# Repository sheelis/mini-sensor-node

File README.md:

# wifi water level transmitter

## Parts:

ESP-WROOM-02 connected to wifi and serving a page, also can send readings to some other server
HC-S04 for distance
DS18B20 for temperature?

## info

how to program ESP-WROOM-02
https://learn.edwinrobotics.com/getting-started-with-esp-wroom-02/
https://www.espressif.com/sites/default/files/documentation/0c-esp-wroom-02_datasheet_en.pdf

3.3v with HC-SR04
https://www.letscontrolit.com/wiki/index.php/HC-SR04

US reading on esp
https://github.com/asksensors/AskSensors-ESP8266-Ultrasonic/blob/master/ultrasonic_http.ino
http://www.esp8266learning.com/wemos-mini-hc-sr04-ultrasonic-sensor.php

https://www.youtube.com/watch?v=Q0eUoFIXrWE

## plan

- kicad and cnc a pcb
- solder on parts
- attach 3.3v transformer
- program blink on esp
- attach US, read distance
- design interface: wifi ap or send to remote server?
- code the transmission, storage, logging

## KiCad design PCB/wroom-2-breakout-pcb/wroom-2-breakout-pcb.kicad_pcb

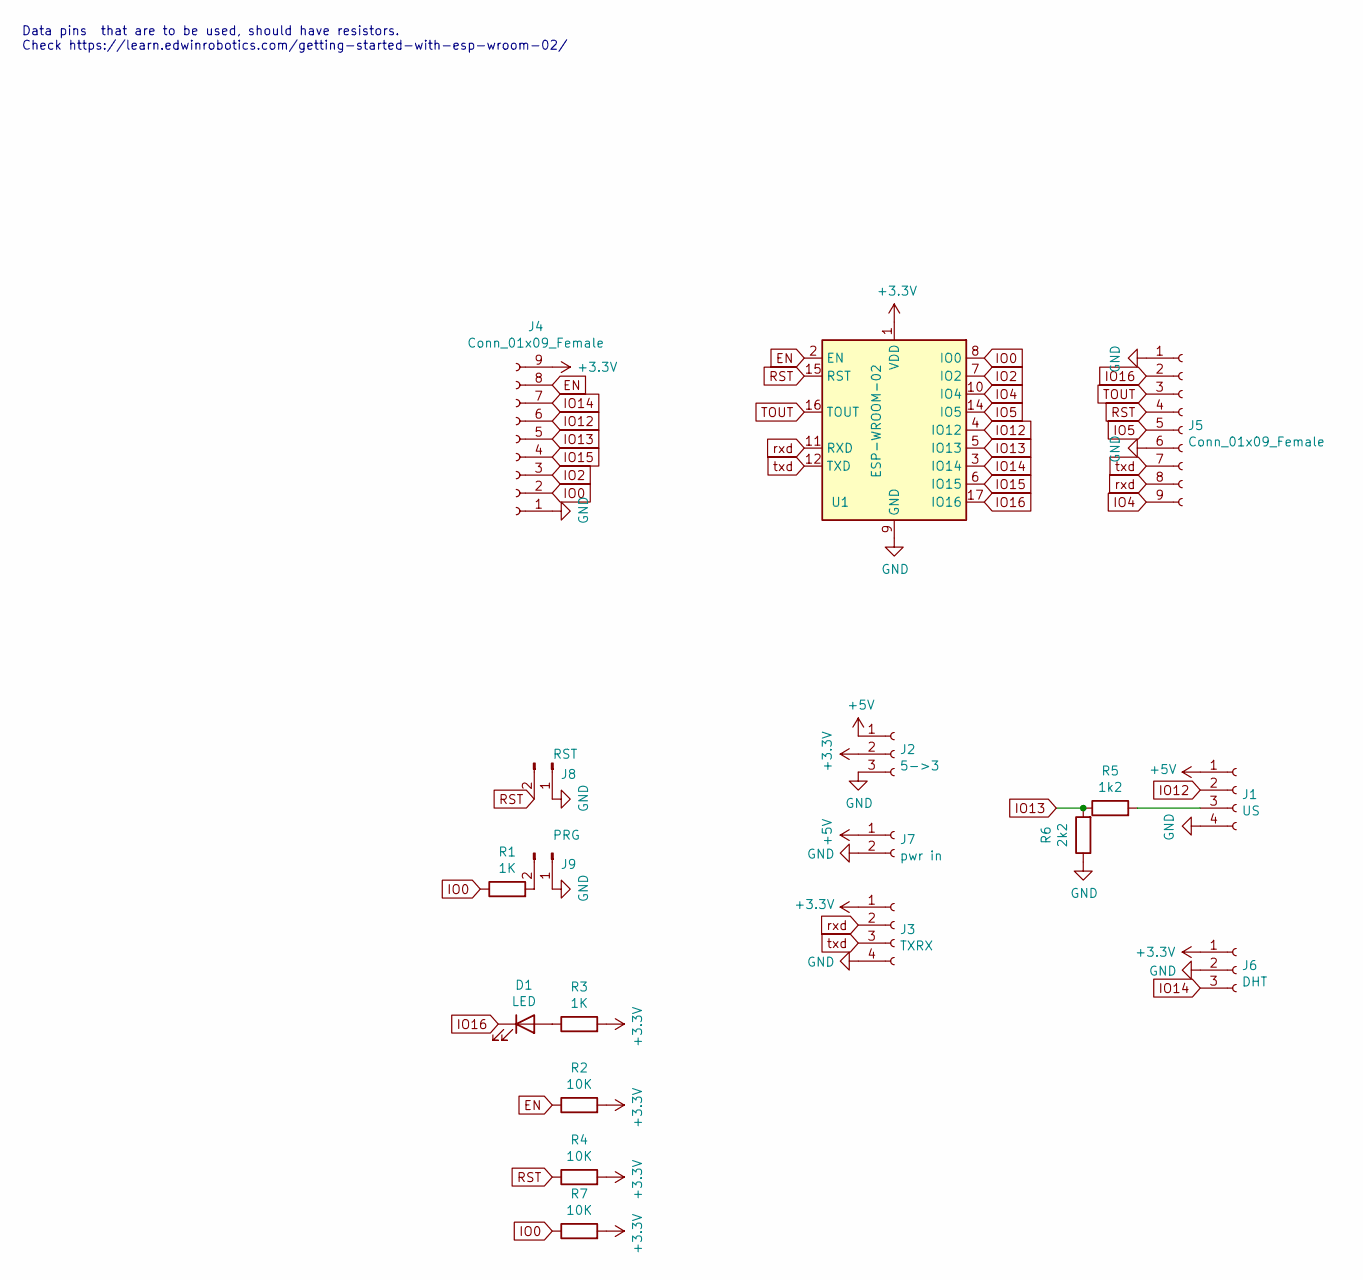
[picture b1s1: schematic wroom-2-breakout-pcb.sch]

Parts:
D1: LED; LED_D3.0mm
J1: US; PinSocket_1x04_P2.54mm_Vertical
J2: 5->3; PinSocket_1x03_P2.54mm_Vertical
J3: TXRX; PinHeader_1x04_P2.54mm_Vertical
J4, J5: Conn_01x09_Female; PinHeader_1x09_P2.54mm_Vertical
J6: DHT; PinHeader_1x03_P2.54mm_Vertical
J7: pwr in; PinHeader_1x02_P2.54mm_Vertical
J8: RST; PinHeader_1x02_P2.54mm_Vertical
J9: PRG; PinHeader_1x02_P2.54mm_Vertical
R1, R3: 1K; R_Axial_DIN0207_L6.3mm_D2.5mm_P7.62mm_Horizontal
R2, R4, R7: 10K; R_Axial_DIN0207_L6.3mm_D2.5mm_P7.62mm_Horizontal
R5: 1k2; R_Axial_DIN0207_L6.3mm_D2.5mm_P7.62mm_Horizontal
R6: 2k2; R_Axial_DIN0207_L6.3mm_D2.5mm_P7.62mm_Horizontal
U1: ESP-WROOM-02

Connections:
+3V3: J2.2, J3.1, J4.9, J6.1, R2.2, R3.2, R4.2, R7.2, U1.1 (VDD)
+5V: J1.1, J2.1, J7.1
EN: J4.8, R2.1, U1.2 (EN)
GND: J1.4, J2.3, J3.4, J4.1, J5.1, J5.6, J6.2, J7.2, J8.1, J9.1, R6.1, U1.9 (GND), U1.13 (GND), U1.18 (GND), U1.19 (GND)
IO0: J4.2, R1.1, R7.1, U1.8 (IO0)
IO2: J4.3, U1.7 (IO2)
IO4: J5.9, U1.10 (IO4)
IO5: J5.5, U1.14 (IO5)
IO12: J1.2, J4.6, U1.4 (IO12)
IO13: J4.5, R5.1, R6.2, U1.5 (IO13)
IO14: J4.7, J6.3, U1.3 (IO14)
IO15: J4.4, U1.6 (IO15)
IO16: D1.1 (K), J5.2, U1.17 (IO16)
unnamed: D1.2 (A), R3.1
unnamed: J1.3, R5.2
unnamed: J9.2, R1.2
RST: J5.4, J8.2, R4.1, U1.15 (RST)
TOUT: J5.3, U1.16 (TOUT)
rxd: J3.2, J5.8, U1.11 (RXD)
txd: J3.3, J5.7, U1.12 (TXD)

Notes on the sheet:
Data pins that are to be used, should have resistors. Check https://learn.edwinrobotics.com/getting-started-with-esp-wroom-02/

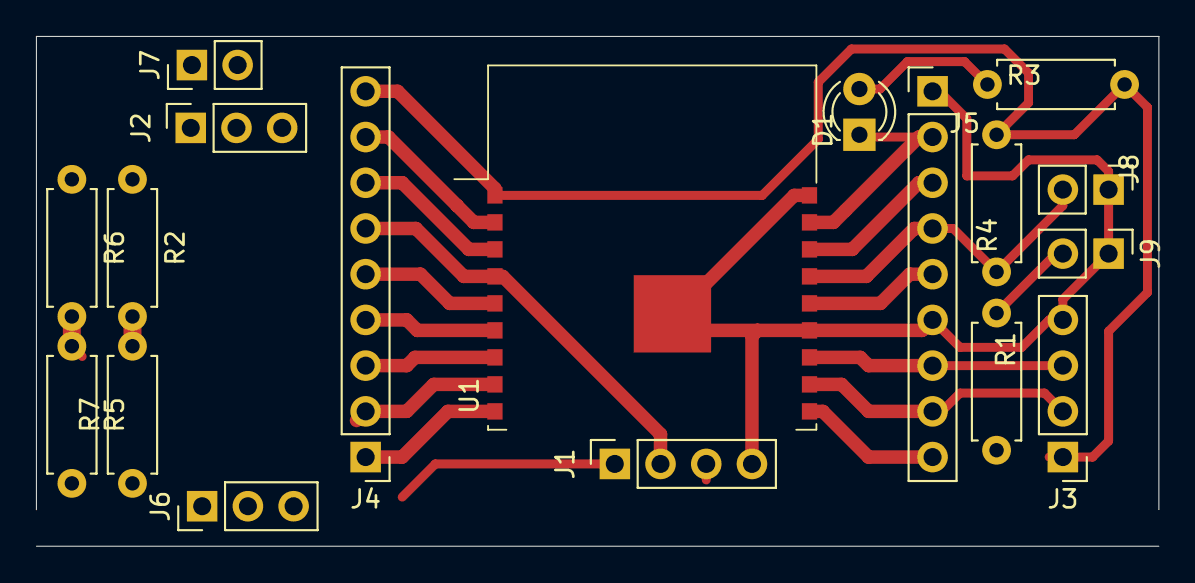
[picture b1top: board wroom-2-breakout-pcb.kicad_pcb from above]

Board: 2 copper layers, 62.4 x 28.3 mm, 18 parts (0 on the bottom side), 20 nets.
